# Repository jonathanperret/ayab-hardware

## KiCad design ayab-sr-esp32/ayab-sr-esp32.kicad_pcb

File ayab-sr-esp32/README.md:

# AYAB-SR-ESP32

ESP32-S3 interface board for Silver Reed knitting machines (successor of the
`ayab-silver-reed-shield` in `silverreed-firmware`). KiCad 10 project.
AYAB talks to it over Wi-Fi in normal use; USB (J2) is the fallback for users
who prefer a cable, and for flashing.

Status: schematic complete, board placed and routed (DRC: 0 unconnected, no
clearance errors). Not built yet — see *Open points* before ordering.

The schematic is a single A2 sheet split into titled sections: power input,
5 V buck, 3.3 V supply, USB (programming), user interface, solenoid buck,
current sense and limiter, mechanical, MCU, level shifting and machine
connector. Sections connect through net labels.

## Power

| Rail | Source | Notes |
|---|---|---|
| `+15V` | J1 USB-C PD, CH224A (U1) asks for 15 V, set by R1 = 56k alone (I²C not used) | Feeds both bucks |
| `Vout` / `Vsol` | U6 TPS54202; Q1 bypasses it (≈ 15 V) until an overcurrent, then it regulates at 8.05 V (R4/R24/R5 = 100k/3.3k/4.7k) | Solenoid supply, through shunt R6 (50 mΩ); `Vsol` goes to the DIN socket |
| `+5V` | U9 TPS54202, R12/R13 = 75k/10k → 5.07 V | Machine logic (DIN pin 7), U4, pull-ups R15–R18 |
| `+3.3V` | U10 AP2112K from `+5V` (D2) or J2 VBUS (D1) | ESP32, OLED, U7, U8 |

- U6 (solenoids) is enabled by the ESP32 (`SOL_EN`, 100k pull-down: off until
  the firmware turns it on). U9 is always on.
- Current limiter: U7 INA381A1 senses R6 (Kelvin connection), compares with
  a fixed threshold, and its `ALERT` output switches Q1, which pulls
  U6's FB to ground. `Vsense` (U7 VOUT, 1 V/A) is read by the ESP32.
  Threshold: R9 82k / R25 10k / R26 7.5k / R23 27k on 3.3 V gives CMPREF
  0.90 V, i.e. 0.90 A (starting values, to be confirmed on the silverreed shield;
  R24 sets the 8 V fallback, R25/R26 the threshold).
  Why 8 V: a solenoid is about 7 Ω cold (a little more once warm), so 0.9 A
  takes 6.3 V across it, plus the VCE of the carriage's Darlington driver and
  the drop in the DIN cable to the carriage.
  Hysteresis 4 µA × (12.5k + R10 82k) ≈ 0.38 V, i.e. ~0.4 A; CMPREF (0.90 V)
  stays above it, so `ALERT` always releases (RESET is tied
  to GND).

## ESP32-S3-WROOM-1 pin map

| GPIO | Module pin | Signal | Direction / notes |
|---|---|---|---|
| IO0 | 27 | `BTN_C` | S1 push (centre); also the BOOT strap: held at reset → download mode |
| IO1 | 39 | `Vsense` | ADC1_CH0, U7 output, 1 V per amp of solenoid current |
| IO2 | 38 | `Vsol_div` | ADC1_CH1, `Vsol` × 10/57 (R7 47k / R8 10k): 15 V → 2.63 V |
| IO8 | 12 | `SDA` | I²C, OLED (U5) only, 4.7k pull-ups R21/R22 |
| IO18 | 11 | `SCL` | I²C |
| IO9 | 17 | `ND1_3V` | Machine ND1 via U8 |
| IO10 | 18 | `CCP_3V` | Machine CCP (carriage clock) via U8 |
| IO11 | 19 | `HOK_3V` | Machine HOK (direction) via U8 |
| IO13 | 21 | `KSL_3V` | Machine KSL (point cam) via U8 |
| IO14 | 22 | `DOB_3V` | Output: solenoid data, to the DIN via U4 (5 V) |
| IO16 | 9 | `BTN_B` | S1 rolled toward the USB-C edge (away from the DIN) |
| IO17 | 10 | `BTN_D` | S1 rolled toward the DIN |
| IO38 | 31 | `SOL_EN` | Output: enable of the solenoid buck U6 (high = on) |
| IO39 | 32 | `PG` | CH224A power-good (open drain, 10k pull-up) |
| IO19/IO20 | 13/14 | USB D−/D+ | Native USB on J2 (through U2 ESD) |
| TXD0/RXD0 | 37/36 | J4 | UART header, not populated by default |

Firmware notes:

- Machine inputs: U8 (74LVC125, powered from 3.3 V, 5 V-tolerant inputs)
  translates the 5 V DIN signals; R15–R18 pull them up to 5 V on the DIN side,
  so `INPUT` is enough on the ESP32 side (no internal pull-up needed).
- `DOB`: U4 (74AHCT1G125 on 5 V) drives the DIN from the 3.3 V GPIO.
- Buttons: S1 common is GND → `INPUT_PULLUP`, active low.
- Avoided on purpose: IO3, IO45, IO46 (straps), IO35–IO37 (PSRAM on some
  module variants).
- The I²C bus is the OLED's only: the CH224A's CFG2/CFG3 are left open
  (single-resistor mode, R1 alone requests 15 V). Unpowered, the CH224A would
  pull them toward its dead supply (internal pull-ups) and hold the bus at
  about 2 V, below the ESP32's and the SSD1306's VIH.
- The ESP32 and the display also run with only J2 plugged in (`+3.3V` from J2
  VBUS through D1 and U10). A PD adapter plugged into J2 instead of J1 can be
  detected: `PG` stays high (the CH224A is unpowered) and no USB host enumerates
  the ESP32.

## Connectors

| Ref | Function |
|---|---|
| J1 | USB-C, power input (USB-PD 15 V) |
| J2 | USB-C, ESP32 native USB (programming, serial) |

J1 and J2 are 14.8 mm apart (centre to centre), like the USB-C ports of a
MacBook, so dual-plug MacBook cables and hubs fit both at once.
| J3 | DIN-7 female, to the knitting machine |
| J14 | 1×8 header duplicating the DIN signals (debug / alternative cable) |
| J4 | ESP32 UART0 (TX, RX), not populated |
| S1 | BL-DT 3-way thumb wheel, wheel protrudes past the top edge, under the OLED. Per the datasheet, rolling the rim 24° toward a terminal's side closes it: toward the USB-C edge → B, toward the DIN → D; push → C (common A to GND) |
| U5 | 0.91" 128×32 I²C OLED module, Hansheng HS91L02W2C01 (LCSC C5248081, SSD1306, address 0x3C), plugged into J15 on its own 2.5 mm pin spacer; any 38 × 12 mm 4-pin GND/VCC/SCL/SDA module fits. Not in the JLCPCB BOM nor the CPL: bought separately and fitted at assembly (see *Assembly-time parts*). Its far end overhangs the board edge and rests on a block of the enclosure tray |
| J15 | Low-profile 1×4 2.54 mm female socket for U5, 5.0 mm high (HC-PM254-5.0H-1x4PZ-02A, LCSC C42163122; standard sockets are 8.5 mm) |

DIN J3 and J14 pinout:

| Signal | J3 | J14 |
|---|---|---|
| ND1 | 1 | 2 |
| KSL | 2 | 3 |
| DOB | 3 | 4 |
| CCP | 4 | 5 |
| HOK | 5 | 6 |
| Vsol | 6 | 7 |
| +5V | 7 | 8 |
| GND | shield (8) | 1 |

## PCB

- 2 layers, GND pour on both sides, 64.5 × 97.1 mm (width × height), drawn in
  its intended orientation: DIN socket J3 facing up, USB-C sockets on the
  right edge. A 23.9 × 8.7 mm notch above the DIN socket leaves room for bulky
  plugs. S1's wheel sticks out of the top edge, centred on its straight part
  (x 123.9–164.5 before the antenna-side cut, see below); the OLED's visible area sits 0.5 mm further from the DIN
  than S1's axis (the HS91L02W2C01 active area is 7.62 mm from the end of
  its board, not the 7.1 mm the board was laid out for).
- Net classes: Power 0.6 mm (`+15V`, U6 switch node, `Vout`, `Vsol`),
  Supply 0.3 mm (`+5V`, `+3.3V`, LDO input, J2 VBUS), Default 0.2 mm.
- Minimum track 0.15 mm (fine-pitch escapes), minimum hole 0.2 mm (ESP32
  footprint thermal vias): within JLCPCB's standard process.
- Antenna: the ESP32 antenna is on the right edge, with a 5.6 × 47.9 mm
  cut-out under it (y 38.7–86.6, from x = 158.9: the keep-out starts at
  158.66, the 0.24 mm strip left keeps the SDA/SCL tracks 0.5 mm from the
  edge). The board was lengthened by 6 mm at the bottom so that the OLED
  module clears the keep-out: the top components (J3, U5, S1) and the top
  edge stayed in place, everything else moved down 6 mm (U5's courtyard ends
  at y 38.55, the keep-out starts at 38.7). Above the cut-out, the board is
  cut along the same line (x = 158.9) up to the top edge: the far end of the
  OLED module overhangs the board there by 5 mm and rests on a block of the
  enclosure tray. The board was then lengthened by 8 mm more at the bottom
  (nothing moved but the bottom edge and the holes).
- Mounting holes (M3, GND pad): H1 and H3 in the two bottom corners, 5.4 mm
  from the side edges and 5.3 mm from the bottom (105.4 / 116.8 and
  159.1 / 116.8), and H2 below the OLED near the right edge (155.4 / 44.5: as far
  right as the antenna keep-out allows, its lid column 2.9 mm from the OLED module).
- Routing: [UltraRoute](https://github.com/sequoia-hope/ultraroute) (commit `ddc2375`), following
  the phase-7 method of [Boardroom](https://github.com/sequoia-hope/boardroom)'s design skill,
  adapted to 2 layers and kept to 0/45/90-degree tracks. It lays the board out from bare pads, so a
  re-route is reproducible:
  - Before routing: the mechanically fixed parts locked (J1–J3, J15, U5, S1, U3, H1–H3); the GND
    pour on B.Cu only, as a soft plane (crossing it costs, `--pour-cost 3`); a GND via at every
    SMD ground pad; short links drawn from pad positions: the Kelvin pair from the inner side of
    shunt R6's pads to U7, and 0.5 mm stubs out of J1's VBUS pads; edge strips (no tracks or vias,
    pours allowed) between the USB-C, DIN and J14 pads and the board edge.
  - Rules in `ayab-sr-esp32.kicad_dru`, which both the router and KiCad's DRC apply: Power class
    at least 0.4 mm (0.6 where there is room), Supply at least 0.25 mm (0.3), except the Kelvin
    tracks inside the `kelvin-u7` area.
  - Router stages: UltraRoute's default recipe without `--tighten` (which pulls the copper taut at
    any angle) and without `--diff-pairs` (its coupled pairs are laid at any angle too; the ESP32-S3's
    USB is full-speed only, about 40 mm here, and needs no coupled routing):
    `--negotiate --rip-up --rip-boxed --prefanout --escape-room --shove-plough region --shove-reach 0.5
    --shove-repair 20 --shove-ties --guard-ties --shove-passes 60 --shove-patience 8 --strip
    --pour-cost 3 --seed N --threads 1 --timeout 240`, nice'd, one run at a time.
  - Seeds 0–9 tried, each judged by KiCad after restoring the F.Cu pour and refilling (all clean);
    seed 9 kept for its short 15 V buck switch node (11.1 mm, no via) and bootstrap (1.9 mm, no
    via: C4 sits beside U6, its pads 2.7 mm from BOOT and 3.6 mm from SW).
  - After routing: GND pours on both sides, stitching vias on a 3 mm grid, dangling copper
    removed, all copper unlocked (only the parts above stay locked); then `octofix.py` turns every
    segment off a multiple of 45 degrees into a 45-degree leg and an orthogonal leg (ends unmoved,
    the variant KiCad's DRC accepts), and collinear pieces are merged. 99.7% of the track length is
    at 0/45/90 degrees; what is left is 32 pad entries of at most 0.3 mm and 2 short jogs.
  - Checks: DRC 0 errors and 0 unconnected with every severity on (`min_connection` 0.127 mm;
    dangling tracks and vias, slivers, isolated copper and connection width as errors); every pad's
    best joint at least min(0.15 mm, track width); B.Cu ground in one piece (5138 mm²), stitched to
    the F.Cu pour.
  - Against the Freerouting route: 2093 mm of track instead of 2059 mm, 79 signal and power
    vias plus 452 GND vias (45 at ground pads, the rest stitching), B.Cu ground in 1 piece instead of 14, and power tracks at
    their class widths (the old route had 90 power tracks under them).
  - The driver and the board's routing inputs are on the `tooling` branch
    (`scripts/kicad/route/ultraroute/`, `ayab-sr-esp32/tools/ultraroute/`): `route.sh ayab-sr-esp32 WORK 9`,
    then `finish.sh WORK/j9 WORK/final`, regenerates this board.
  - Placement finding: J1's VBUS pads sit between the CC pins, so its stubs are 0.5 mm, not 0.6.

3D models: `ayab-library/packages3D/OLED_0.91_128x32_I2C.step` (generated by
`packages3D/generators/oled_0.91_128x32_step.py`, raised 5 mm by the U5 footprint for the socket),
`PinSocket_1x04_P2.54mm_Vertical_H5.0.step` for J15 (`packages3D/generators/pin_socket_1x04_h5_step.py`) and `SW-SMD_BL-DT.step` for S1 (CadQuery,
`packages3D/generators/sw_smd_bl_dt_step.py`, from the manufacturer's drawing).

A 3D-printable enclosure is in [`enclosure/`](enclosure/README.md).
Its model follows the board's 90° turn (`board_frame()` in the .scad), the
current outline and holes, the OLED on its 5 mm socket (lid raised by 5 mm) and the block under
the OLED's far end. A redesign is planned (ring around the machine's mast).

## Renders

Board renders come from KiCad (`kicad-cli pcb render`), enclosure renders from
OpenSCAD's preview (`enclosure/tools/quick_render.py`) and the 2D sections
from `enclosure/tools/sections.py`. MP4 versions of the enclosure animations:
[turntable](enclosure/renders/turntable.mp4),
[exploded](enclosure/renders/exploded.mp4).

### Interactive 3D view

[`viewer/`](viewer/) is a three.js page: the board (KiCad GLB export with
silkscreen and soldermask) in its tray and lid, with orbit and zoom, an explode
slider, preset views, toggles for the silkscreen and the copper traces
(`traces.json`, drawn at their true width but raised 0.1 mm and coloured: copper
on top, blue underneath), and a click on a part shows its reference, value and
LCSC number. It needs to be served
over HTTP, e.g. GitHub Pages, or locally:

    python3 -m http.server -d ayab-sr-esp32/viewer 8000   # then open http://localhost:8000

### Board

<table>
<tr><td align="center"><br><sub>Front isometric</sub></td><td align="center"><br><sub>Back isometric</sub></td></tr>
<tr><td align="center"><br><sub>Top</sub></td><td align="center"><br><sub>Bottom</sub></td></tr>
</table>

### Enclosure

<table>
<tr><td align="center"><br><sub>Assembled</sub></td><td align="center"><br><sub>Assembled, DIN and wheel side</sub></td></tr>
<tr><td align="center"><br><sub>X-ray (transparent lid)</sub></td><td align="center"><br><sub>Exploded</sub></td></tr>
<tr><td align="center"><br><sub>Tray with the board</sub></td><td align="center"><br><sub>Tray</sub></td></tr>
<tr><td align="center"><br><sub>Lid, top</sub></td><td align="center"><br><sub>Lid, underside</sub></td></tr>
<tr><td align="center"><br><sub>USB-C side</sub></td><td align="center"><br><sub>DIN and wheel side</sub></td></tr>
<tr><td align="center"><br><sub>Turntable</sub></td><td align="center"><br><sub>Exploded, animated</sub></td></tr>
</table>

### Enclosure sections

<table>
<tr><td align="center"><br><sub>Through the wheel S1 and the OLED</sub></td><td align="center"><br><sub>Through the DIN socket axis</sub></td></tr>
<tr><td align="center"><br><sub>Through the USB-C J1</sub></td><td align="center"><br><sub>Through the H2 column</sub></td></tr>
<tr><td align="center"><br><sub>Through the OLED support block</sub></td><td></td></tr>
</table>

## Production files

`production/` holds outputs generated with `kicad-cli` 10.0.7 from this
revision: Gerbers and Excellon drill files (`gerbers/`, zipped in
`ayab-sr-esp32-gerbers.zip`), the BOM (`ayab-sr-esp32-bom.csv`, grouped, with
an LCSC number on every placed part), the pick-and-place file
(`ayab-sr-esp32-pos.csv`, plus `ayab-sr-esp32-cpl-jlc.csv` in JLCPCB's CPL format with
the `FT Rotation Offset` corrections applied) and the schematic PDF. Regenerate them after
any change (scripts on the `tooling` branch).

### Ordering the parts from LCSC (self-assembly)

The BOM's LCSC numbers are chosen for JLCPCB assembly (basic parts where possible). For a direct
LCSC order, one substitute applies while LCSC's own stock of the BOM part is empty:

- **C3, C12, C14, C15** (100 nF 0603, BOM C14663, a JLCPCB basic part with plenty of JLCPCB
  stock): order **C1591** (Samsung CL10B104KB8NNNC, 100 nF X7R 50 V 0603) from LCSC instead.
  Keep C14663 in the BOM: C1591 is an extended part at JLCPCB (about $3 more per assembly order).

Parts for 5 boards cost about $56 at LCSC (November 2026 prices, minimum order quantities
applied, OLED module, shipping and import duties not included).

## Assembly-time parts

JLCPCB assembles everything in the BOM and CPL, J15 included. One part is not in either and is
fitted by the assembler:

- **OLED module U5**: 0.91" 128×32 I²C module (Hansheng HS91L02W2C01, LCSC C5248081, or any
  38 × 12 mm SSD1306 module), 3.3 V supply, 4 pins at 2.54 mm in the order **GND, VCC, SCL, SDA**
  (pin 1 = GND: the square pad of J15, the one farthest from the top edge). It needs a 4-pin male header
  soldered on: check whether your module comes with the header soldered (the LCSC part appears to
  ship without one, going by its datasheet drawing).
- **Fitting**: plug it into J15 (5.0 mm low-profile socket), glass up, the module overhanging the
  board edge on the antenna side. The header's 2.5 mm plastic spacer rests on top of J15; the pins
  below it go into the socket, whose contacts are about 4.5 mm deep. Standard headers have about
  6 mm below the spacer: if the module does not sit flat on the socket, trim the pins to about
  4 mm below the spacer. The enclosure has no trimming jig.
- **Support**: the far end of the module rests on a block of the enclosure tray (0.1 mm below the
  module), in the space next to the board edge.

## Tooling

The scripts used to edit, check, route and regenerate this board (and the matching workflow skill)
live on the `tooling` branch.

## Open points

- CH224A (checked in the WCH CH224 manual v2.1): PG is open drain, active low,
  rated 32 V, so R20 is right; CFG2/CFG3 may float in single-resistor mode
  (§5.2.1), so they are left unconnected.
- Wi-Fi is the main link, so the antenna matters most. The OLED module is
  now clear of the antenna keep-out. On the first boards, measure RSSI and
  throughput with the board in its enclosure and mounted on the machine (a
  large metal body: the antenna end should face away from it). If range is
  short: use the ESP32-S3-WROOM-1U (u.FL) with a small external antenna
  (about $0.5–1 more).
- Also on the first boards: scope the 3.3 V rail during Wi-Fi transmit bursts
  (350–500 mA peaks on the AP2112K) with the solenoids firing, the bucks'
  switching noise, and the Vsense / Vsol_div ADC readings. These measurements
  decide whether the first respin goes to 4 layers (solid GND plane under
  the module and the bucks).
- DRC: clean. `ayab-sr-esp32.kicad_dru` has
  the JLCPCB 2-layer rules plus two documented exceptions: U5 stands on its
  socket above J15 and S1 (courtyard overlap), and the silkscreen of parts
  that overhang the board edge (U3, U5, J3) is clipped by the fab.

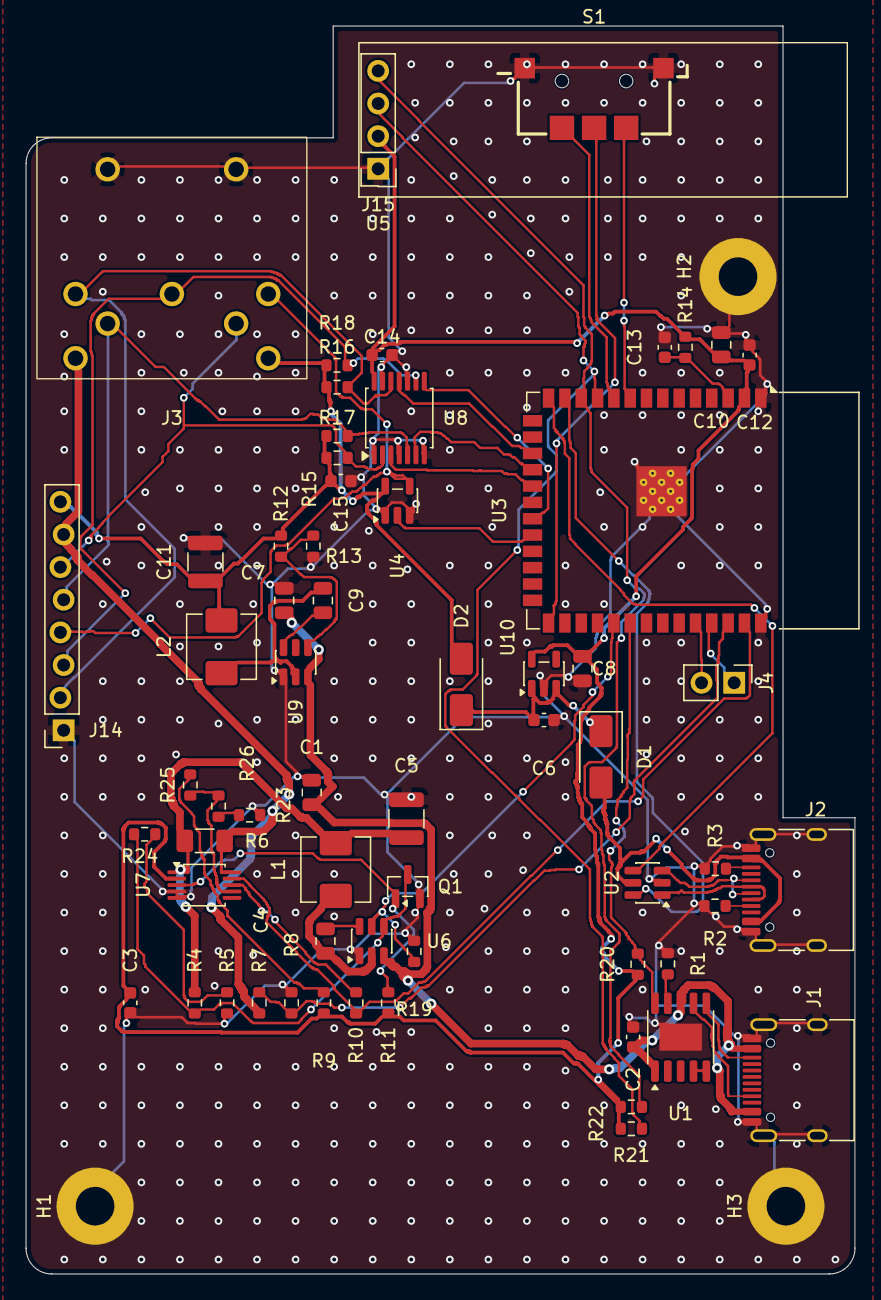
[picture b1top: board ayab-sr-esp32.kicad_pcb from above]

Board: 2 copper layers, 64.5 x 97.1 mm, 66 parts (0 on the bottom side), 52 nets.

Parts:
C1, C7, C8: 10u; C_0805_2012Metric
C2, C6, C13: 1u; C_0603_1608Metric
C3, C12, C14, C15: 100n; C_0603_1608Metric
C4, C9: 100n; C_0805_2012Metric
C5, C11: 47u; C_1210_3225Metric
C10: 22u; C_0805_2012Metric
D1, D2: SS34; D_SMA
H1, H2, H3: MountingHole_Pad; MountingHole_3mm_Pad
J1, J2: USB_C_Receptacle_USB2.0_16P; USB_C_Receptacle_HRO_TYPE-C-31-M-12
J3: DIN-7; DIN-704-M10
J4: Conn_01x02; PinHeader_1x02_P2.54mm_Vertical
J14: Conn_01x08; PinSocket_1x08_P2.54mm_Vertical_Lock
J15: HC-PM254-5.0H-1x4PZ-02A; PinSocket_1x04_P2.54mm_Vertical_H5.0
L1, L2: 10u; L_Changjiang_FXL0518
Q1: BSS138; SOT-23
R1: 56k; R_0603_1608Metric
R2, R3: 5.1k; R_0603_1608Metric
R4, R19: 100k; R_0603_1608Metric
R5, R21, R22: 4.7k; R_0603_1608Metric
R6: 50m; R_1206_3216Metric_Pad1.30x1.75mm_HandSolder
R7: 47k; R_0603_1608Metric
R8, R11, R13, R14, R15, R16, R17, R18, R20, R25: 10k; R_0603_1608Metric
R9, R10: 82k; R_0603_1608Metric
R12: 75k; R_0603_1608Metric
R23: 27k; R_0603_1608Metric
R24: 3.3k; R_0603_1608Metric
R26: 7.5k; R_0603_1608Metric
S1: BL-DT; SW-SMD_BL-DT
U1: CH224A; SSOP-10-1EP_3.9x4.9mm_P1mm_EP2.1x3.3mm
U2: USBLC6-2SC6; SOT-23-6
U3: ESP32-S3-WROOM-1
U4: 74AHCT1G125; SOT-23-5
U5: HS91L02W2C01; OLED_0.91_128x32_I2C_Module_Socket_H5.0
U6, U9: TPS54202; SOT-23-6
U7: INA381A1; TSSOP-10_3x3mm_P0.5mm
U8: 74LVC125; TSSOP-14_4.4x5mm_P0.65mm
U10: AP2112K-3.3; SOT-23-5

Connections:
+3.3V: C3.2, C8.1, C10.1, C12.1, C14.1, J15.2, R9.1, R11.1, R14.1, R20.1, R21.1, R22.1, U3.2 (3V3), U7.2 (VS), U8.14 (VCC), U10.5 (VOUT)
+5V: C11.1, C15.2, D2.2 (A), J3.7, J14.8, L2.2, R12.2, R15.1, R16.1, R17.1, R18.1, U4.5 (VCC)
+15V: C1.1, C2.1, C7.1, J1.A4 (VBUS), J1.A9 (VBUS), J1.B4 (VBUS), J1.B9 (VBUS), U1.1 (VHV), U1.8 (VBUS), U6.3 (VIN), U9.3 (VIN)
/ALERT: Q1.1 (G), R11.2, U7.3 (~ALERT)
/BTN_B: S1.B, U3.9 (IO16)
/BTN_C: S1.C, U3.27 (IO0)
/BTN_D: S1.D, U3.10 (IO17)
/CCP: J3.4, J14.5, R17.2, U8.5 (2A)
/CCP_3V: U3.18 (IO10), U8.6 (2Y)
/CFG1: R1.1, U1.9 (CFG1)
/CMPREF: R25.2, R26.1, U7.7 (CMPREF)
/DOB: J3.3, J14.4, U4.4
/DOB_3V: U3.22 (IO14), U4.2
/FB: Q1.3 (D), R4.1, R24.1, U6.4 (FB)
/HOK: J3.5, J14.6, R15.2, U8.2 (1A)
/HOK_3V: U3.19 (IO11), U8.3 (1Y)
/KSL: J3.2, J14.3, R16.2, U8.9 (3A)
/KSL_3V: U3.21 (IO13), U8.8 (3Y)
/ND1: J3.1, J14.2, R18.2, U8.12 (4A)
/ND1_3V: U3.17 (IO9), U8.11 (4Y)
/PG: R20.2, U1.10 (PG), U3.32 (IO39)
/SCL: J15.3, R22.2, U3.11 (IO18)
/SDA: J15.4, R21.2, U3.12 (IO8)
/SOL_EN: R19.1, U3.31 (IO38), U6.5 (EN)
/USB2_VBUS: D1.2 (A), J2.A4 (VBUS), J2.A9 (VBUS), J2.B4 (VBUS), J2.B9 (VBUS), U2.5 (VBUS)
/USB_DM: U2.6 (I/O1), U3.13 (USB_D-)
/USB_DP: U2.4 (I/O2), U3.14 (USB_D+)
/Vout: C5.1, L1.2, R4.2, R6.1, U7.1 (IN+)
/Vsense: R10.1, U3.39 (IO1), U7.9 (VOUT)
/Vsol: J3.6, J14.7, R6.2, R7.1, U7.10 (IN-)
/Vsol_div: R7.2, R8.1, U3.38 (IO2)
GND: C1.2, C2.2, C3.1, C5.2, C6.2, C7.2, C8.2, C10.2, C11.2, C12.2, C13.2, C14.2, C15.1, H1.1 (1_1), H2.1 (1_1), H3.1 (1_1), J1.A1 (GND), J1.A12 (GND), J1.B1 (GND), J1.B12 (GND), J1.SH (SHIELD), J2.A1 (GND), J2.A12 (GND), J2.B1 (GND), J2.B12 (GND), J2.SH (SHIELD), J3.8 (GND_8), J14.1, J15.1, Q1.2 (S), R1.2, R2.2, R3.2, R5.1, R8.2, R13.1, R19.2, R23.2, S1.A, U1.11 (GND), U2.2 (GND), U3.1 (GND), U3.40 (GND), U3.41 (GND), U4.1, U4.3 (GND), U6.1 (GND), U7.4 (RESET), U7.5 (GND), U8.1 (~1OE), U8.4 (~2OE), U8.7 (GND), U8.10 (~3OE), U8.13 (~4OE), U9.1 (GND), U10.2 (GND)
unnamed: C6.1, D1.1 (K), D2.1 (K), U10.1 (VIN), U10.3 (EN)
unnamed: J1.A5 (CC1), U1.7 (CC1)
unnamed: J1.B5 (CC2), U1.6 (CC2)
unnamed: J2.A5 (CC1), R2.1
unnamed: J2.B5 (CC2), R3.1
unnamed: J2.A6 (D+), J2.B6 (D+), U2.3 (I/O2)
unnamed: J2.A7 (D-), J2.B7 (D-), U2.1 (I/O1)
unnamed: J4.1, U3.37 (TXD0)
unnamed: J4.2, U3.36 (RXD0)
unnamed: R23.1, R26.2
unnamed: R5.2, R24.2
unnamed: R9.2, R25.1
unnamed: U1.4 (DP), U1.5 (DM)
unnamed: C13.1, R14.2, U3.3 (EN)
unnamed: C4.1, U6.6 (BOOT)
unnamed: C4.2, L1.1, U6.2 (SW)
unnamed: R10.2, U7.8 (CMPIN)
unnamed: C9.1, U9.6 (BOOT)
unnamed: R12.1, R13.2, U9.4 (FB)
unnamed: C9.2, L2.1, U9.2 (SW)

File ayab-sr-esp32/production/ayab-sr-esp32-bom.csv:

"Designator","Value","Footprint","LCSC","Qty","DNP"
"C1,C7,C8","10u","Capacitor_SMD:C_0805_2012Metric","C15850","3",""
"C2,C6,C13","1u","Capacitor_SMD:C_0603_1608Metric","C15849","3",""
"C3,C12,C14,C15","100n","Capacitor_SMD:C_0603_1608Metric","C14663","4",""
"C4,C9","100n","Capacitor_SMD:C_0805_2012Metric","C49678","2",""
"C5,C11","47u","Capacitor_SMD:C_1210_3225Metric","C7432791","2",""
"C10","22u","Capacitor_SMD:C_0805_2012Metric","C45783","1",""
"D1,D2","SS34","Diode_SMD:D_SMA","C8678","2",""
"J1,J2","USB_C_Receptacle_USB2.0_16P","Connector_USB:USB_C_Receptacle_HRO_TYPE-C-31-M-12","C165948","2",""
"J3","DIN-7","Library:DIN-704-M10","C20611695","1",""
"J15","HC-PM254-5.0H-1x4PZ-02A","Library:PinSocket_1x04_P2.54mm_Vertical_H5.0","C42163122","1",""
"L1,L2","10u","Inductor_SMD:L_Changjiang_FXL0518","C475910","2",""
"Q1","BSS138","Package_TO_SOT_SMD:SOT-23","C7420339","1",""
"R1","56k","Resistor_SMD:R_0603_1608Metric","C23206","1",""
"R2,R3","5.1k","Resistor_SMD:R_0603_1608Metric","C23186","2",""
"R4,R19","100k","Resistor_SMD:R_0603_1608Metric","C25803","2",""
"R5,R21,R22","4.7k","Resistor_SMD:R_0603_1608Metric","C23162","3",""
"R6","50m","Resistor_SMD:R_1206_3216Metric_Pad1.30x1.75mm_HandSolder","C127691","1",""
"R7","47k","Resistor_SMD:R_0603_1608Metric","C25819","1",""
"R8,R11,R13,R14,R15,R16,R17,R18,R20,R25","10k","Resistor_SMD:R_0603_1608Metric","C25804","10",""
"R9,R10","82k","Resistor_SMD:R_0603_1608Metric","C23254","2",""
"R12","75k","Resistor_SMD:R_0603_1608Metric","C23242","1",""
"R23","27k","Resistor_SMD:R_0603_1608Metric","C22967","1",""
"R24","3.3k","Resistor_SMD:R_0603_1608Metric","C22978","1",""
"R26","7.5k","Resistor_SMD:R_0603_1608Metric","C23234","1",""
"S1","BL-DT","Library:SW-SMD_BL-DT","C53223909","1",""
"U1","CH224A","Package_SO:SSOP-10-1EP_3.9x4.9mm_P1mm_EP2.1x3.3mm","C42459160","1",""
"U2","USBLC6-2SC6","Package_TO_SOT_SMD:SOT-23-6","C2687116","1",""
"U3","ESP32-S3-WROOM-1","RF_Module:ESP32-S3-WROOM-1","C2913198","1",""
"U4","74AHCT1G125","Package_TO_SOT_SMD:SOT-23-5","C52140417","1",""
"U6,U9","TPS54202","Package_TO_SOT_SMD:SOT-23-6","C191884","2",""
"U7","INA381A1","Package_SO:TSSOP-10_3x3mm_P0.5mm","C1849472","1",""
"U8","74LVC125","Package_SO:TSSOP-14_4.4x5mm_P0.65mm","C54411083","1",""
"U10","AP2112K-3.3","Package_TO_SOT_SMD:SOT-23-5","C22365427","1",""

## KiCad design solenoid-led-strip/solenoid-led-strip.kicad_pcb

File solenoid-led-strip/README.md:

# Solenoid LED strip for Brother electronic knitting machines

This board is meant to be used as a debugging aid when working on alternative electronics for the Brother KH-9xx series, such as [AYAB](https://github.com/AllYarnsAreBeautiful). But as it simply inserts itself between the electronics and the solenoids, it can also be used with the machine's original electronics, to understand how they drive the solenoids.

I have not built the board described by this KiCad project yet, only a prototype from the schematic. No guarantee of any kind is offered as to the suitability of these files for producing a working device.

## Prototype board

This board I built uses the same schematic:

## Mockup

## Schematic

## Tracks

## [Interactive view](https://kicanvas.org/?github=https%3A%2F%2Fgithub.com%2Fjonathanperret%2Fayab-hardware%2Ftree%2Fsolenoid-led-strip%2Fsolenoid-led-strip) courtesy of [KiCanvas](https://kicanvas.org)

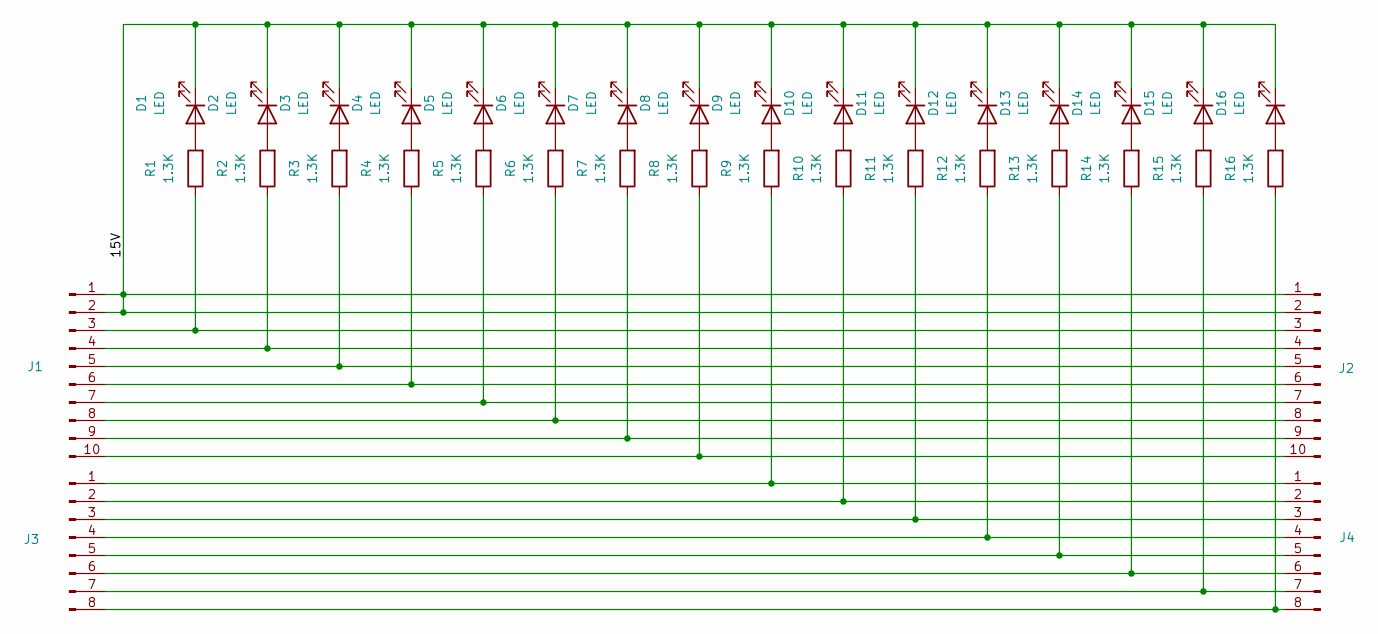
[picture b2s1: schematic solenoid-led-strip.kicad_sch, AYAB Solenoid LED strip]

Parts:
D1, D2, D3, D4, D5, D6, D7, D8, D9, D10, D11, D12, D13, D14, D15, D16: LED; LED_0805_2012Metric
J1: PinHeader_1x10_P2.54mm_Vertical
J2: PinHeader_1x10_P2.54mm_Horizontal
J3: PinHeader_1x08_P2.54mm_Vertical
J4: PinHeader_1x08_P2.54mm_Horizontal
R1, R2, R3, R4, R5, R6, R7, R8, R9, R10, R11, R12, R13, R14, R15, R16: 1.3K; R_0805_2012Metric

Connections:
/15V: D1.1 (K), D2.1 (K), D3.1 (K), D4.1 (K), D5.1 (K), D6.1 (K), D7.1 (K), D8.1 (K), D9.1 (K), D10.1 (K), D11.1 (K), D12.1 (K), D13.1 (K), D14.1 (K), D15.1 (K), D16.1 (K), J1.1, J1.2, J2.1, J2.2
unnamed: D1.2 (A), R1.2
unnamed: D2.2 (A), R2.2
unnamed: D3.2 (A), R3.2
unnamed: D4.2 (A), R4.2
unnamed: D5.2 (A), R5.2
unnamed: D6.2 (A), R6.2
unnamed: D7.2 (A), R7.2
unnamed: D8.2 (A), R8.2
unnamed: D9.2 (A), R9.2
unnamed: D10.2 (A), R10.2
unnamed: D11.2 (A), R11.2
unnamed: D12.2 (A), R12.2
unnamed: D13.2 (A), R13.2
unnamed: D14.2 (A), R14.2
unnamed: D15.2 (A), R15.2
unnamed: D16.2 (A), R16.2
unnamed: J1.3, J2.3, R1.1
unnamed: J1.4, J2.4, R2.1
unnamed: J1.5, J2.5, R3.1
unnamed: J1.6, J2.6, R4.1
unnamed: J1.7, J2.7, R5.1
unnamed: J1.8, J2.8, R6.1
unnamed: J1.9, J2.9, R7.1
unnamed: J1.10, J2.10, R8.1
unnamed: J3.1, J4.1, R9.1
unnamed: J3.2, J4.2, R10.1
unnamed: J3.3, J4.3, R11.1
unnamed: J3.4, J4.4, R12.1
unnamed: J3.5, J4.5, R13.1
unnamed: J3.6, J4.6, R14.1
unnamed: J3.7, J4.7, R15.1
unnamed: J3.8, J4.8, R16.1

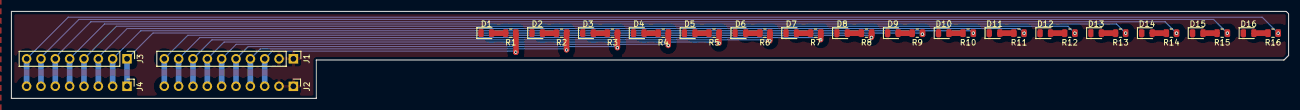
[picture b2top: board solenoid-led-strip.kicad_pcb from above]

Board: 2 copper layers, 226.2 x 15.4 mm, 36 parts (0 on the bottom side), 33 nets.

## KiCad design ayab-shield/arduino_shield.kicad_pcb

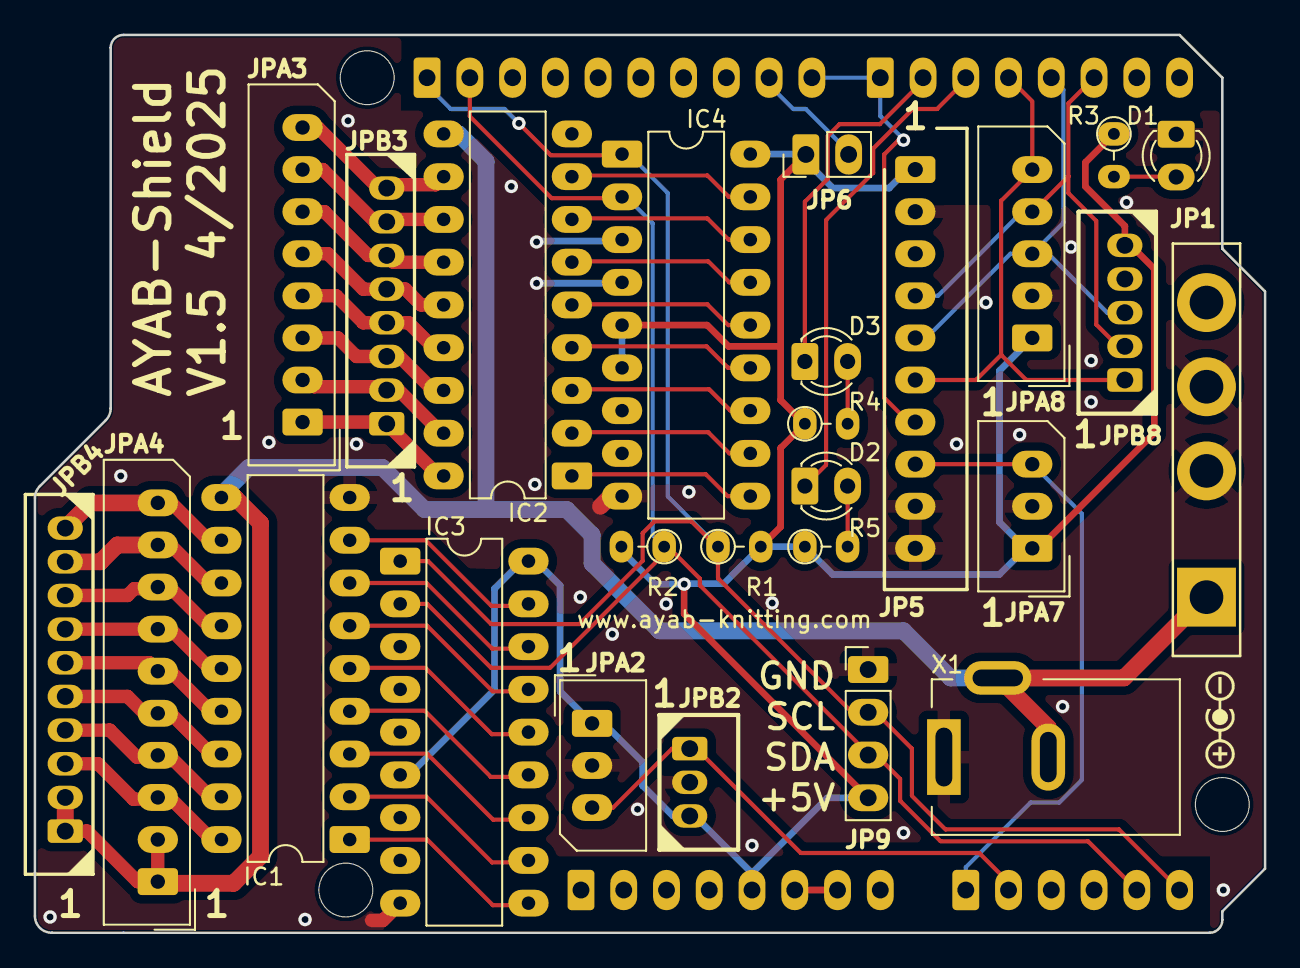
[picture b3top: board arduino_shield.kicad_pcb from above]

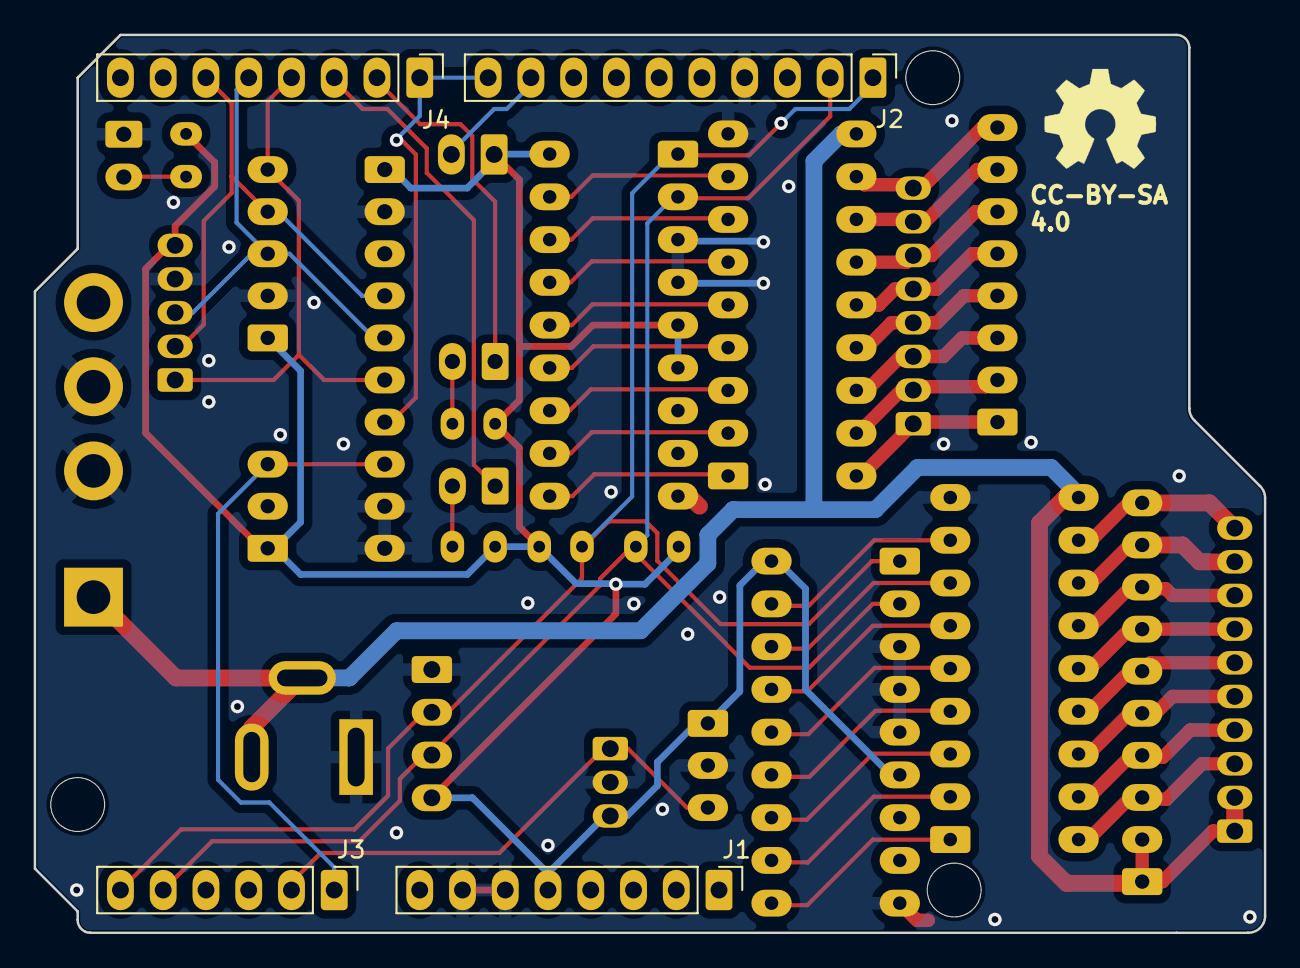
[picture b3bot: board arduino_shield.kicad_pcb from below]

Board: 2 copper layers, 73.1 x 53.3 mm, 33 parts (4 on the bottom side), 49 nets.

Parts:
D1: RED_3MM; LED_D3.0mm
D2: YEL_3MM; LED_D3.0mm
D3: GRN_3MM; LED_D3.0mm
IC1, IC2: ULN2803A; DIP-18_W7.62mm_LongPads
IC3, IC4: MCP2300X/P; DIP-18_W7.62mm_LongPads
J1: Power; PinHeader_1x08_P2.54mm_Vertical
J2: Digital/PWM; PinHeader_1x10_P2.54mm_Vertical
J3: Analog; PinHeader_1x06_P2.54mm_Vertical
J4: Digital/PWM; PinHeader_1x08_P2.54mm_Vertical
JP1: BROTHER POWER; Brother_4P
JP5: 1X10 2.5mm; SHDR10W70P0X250_1X10_2740X490X590P
JP6: 1x2 2.5mm; PinHeader_1x02_P2.54mm_Vertical
JP9: 1X5 2.5mm; PinHeader_1x04_P2.54mm_Vertical
JPA2, JPA7: 1X3 2.5mm; Molex_SPOX_5267-03A_1x03_P2.50mm_Vertical
JPA3: 1X8 2.5mm; Molex_SPOX_5267-08A_1x08_P2.50mm_Vertical
JPA4: 1X10 2.5mm; Molex_SPOX_5267-10A_1x10_P2.50mm_Vertical
JPA8: 1X5 2.5mm; Molex_SPOX_5267-05A_1x05_P2.50mm_Vertical
JPB2: 1X3 2mm; CONN-TH_3P-P2.00_A2004WV-3P
JPB3: 1X8 2mm; 530140810
JPB4: 1X10 2mm; 530141010
JPB8: 1X5 2mm; CONN-TH_A2004WV-5P
MH1, MH2, MH4: MountingHole_3.2mm
R1, R2: 4K7; R_Axial_DIN0204_L3.6mm_D1.6mm_P2.54mm_Vertical
R3, R4, R5: 150; R_Axial_DIN0204_L3.6mm_D1.6mm_P2.54mm_Vertical
X1: KLDX-0202-AC; BarrelJack_Kycon_KLDX-0202-xC_Horizontal

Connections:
+5V: IC3.6 (~RESET), IC3.18 (VDD), IC4.5 (A0), IC4.6 (~RESET), IC4.18 (VDD), J1.5, JP5.1, JP6.1, JP9.4, JPA2.1, JPA7.1, JPA8.1, JPB2.3, JPB8.5, R1.2, R2.2, R3.1, R4.1, R5.1
+15V: IC1.10 (COM), IC2.10 (COM), JP1.1 (+15V), JPA4.1, JPA4.2, JPB4.1, JPB4.2, X1.2, X1.3
/910_L: J2.10, J4.1, JP5.7
/BUZZ: J2.9, JP6.2
/ENC_A: J4.6, JP5.4, JPA8.4, JPB8.2
/ENC_B: J4.5, JP5.5, JPA8.3, JPB8.3
/ENC_C: J4.4, JP5.6, JPA8.5, JPB8.1
/EOL_L: J3.2, JPA2.3, JPB2.1
/EOL_R: J3.1, JP5.8, JPA7.3
/LED_GRN: D3.1 (K), J4.2
/LED_YEL: D2.1 (K), J4.3
/SCL: IC3.1 (SCL), IC4.1 (SCL), J2.1, J3.6, JP9.2, R1.1
/SDA: IC3.2 (SDA), IC4.2 (SDA), J2.2, J3.5, JP9.3, R2.1
GND: D1.1 (K), IC1.9 (GND), IC2.9 (GND), IC3.3 (A2), IC3.4 (A1), IC3.5 (A0), IC3.9 (VSS), IC4.3 (A2), IC4.4 (A1), IC4.9 (VSS), J1.6, J1.7, J2.4, JP1.2 (GND), JP1.3 (GND), JP5.2, JP5.9, JP5.10, JP9.1, JPA2.2, JPA7.2, JPA8.2, JPB2.2, JPB8.4, X1.1
unnamed: D1.2 (A), R3.2
unnamed: D2.2 (A), R5.2
unnamed: D3.2 (A), R4.2
unnamed: IC1.1 (I1), IC3.10 (GP0)
unnamed: IC1.2 (I2), IC3.11 (GP1)
unnamed: IC1.3 (I3), IC3.12 (GP2)
unnamed: IC1.4 (I4), IC3.13 (GP3)
unnamed: IC1.5 (I5), IC3.14 (GP4)
unnamed: IC1.6 (I6), IC3.15 (GP5)
unnamed: IC1.7 (I7), IC3.16 (GP6)
unnamed: IC1.8 (I8), IC3.17 (GP7)
unnamed: IC1.18 (O1), JPA4.3, JPB4.3
unnamed: IC1.17 (O2), JPA4.4, JPB4.4
unnamed: IC1.16 (O3), JPA4.5, JPB4.5
unnamed: IC1.15 (O4), JPA4.6, JPB4.6
unnamed: IC1.14 (O5), JPA4.7, JPB4.7
unnamed: IC1.13 (O6), JPA4.8, JPB4.8
unnamed: IC1.12 (O7), JPA4.9, JPB4.9
unnamed: IC1.11 (O8), JPA4.10, JPB4.10
unnamed: IC2.1 (I1), IC4.10 (GP0)
unnamed: IC2.2 (I2), IC4.11 (GP1)
unnamed: IC2.3 (I3), IC4.12 (GP2)
unnamed: IC2.4 (I4), IC4.13 (GP3)
unnamed: IC2.5 (I5), IC4.14 (GP4)
unnamed: IC2.6 (I6), IC4.15 (GP5)
unnamed: IC2.7 (I7), IC4.16 (GP6)
unnamed: IC2.8 (I8), IC4.17 (GP7)
unnamed: IC2.18 (O1), JPA3.1, JPB3.1
unnamed: IC2.17 (O2), JPA3.2, JPB3.2
unnamed: IC2.16 (O3), JPA3.3, JPB3.3
unnamed: IC2.15 (O4), JPA3.4, JPB3.4
unnamed: IC2.14 (O5), JPA3.5, JPB3.5
unnamed: IC2.13 (O6), JPA3.6, JPB3.6
unnamed: IC2.12 (O7), JPA3.7, JPB3.7
unnamed: IC2.11 (O8), JPA3.8, JPB3.8

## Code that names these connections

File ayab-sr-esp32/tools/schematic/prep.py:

"""Net naming and text fixes, applied to base.kicad_sch (the hand-drawn schematic) before layout.py (old coordinates)."""
import re, sys, uuid
from sx import *
t = open(sys.argv[1]).read()
_n = [0]
def U():
    _n[0] += 1
    return str(uuid.uuid5(uuid.NAMESPACE_URL, "ayab-sr-esp32-prep-%d" % _n[0]))

def label(name, x, y, ang):
    j = 'left bottom' if ang == 0 else 'right bottom'
    return ('\t(label "%s"\n\t\t(at %g %g %d)\n\t\t(effects\n\t\t\t(font\n\t\t\t\t(size 1.27 1.27)\n\t\t\t)\n'
            '\t\t\t(justify %s)\n\t\t)\n\t\t(uuid "%s")\n\t)\n') % (name, x, y, ang, j, U())

def is_wire(s, p, q):
    P = [tuple(map(float, m)) for m in re.findall(r'\(xy ([-\d.]+) ([-\d.]+)\)', s)]
    return head(s) == 'wire' and set(P) == {p, q}

LCSC = {'C2': 'C15849', 'R1': 'C23206', 'R2': 'C23186', 'R3': 'C23186', 'R7': 'C25819', 'R13': 'C25804',
        'D1': 'C8678', 'D2': 'C8678', 'J1': 'C165948', 'J2': 'C165948', 'J3': 'C20611695', 'U1': 'C42459160',
        'U2': 'C2687116', 'U3': 'C2913198', 'U4': 'C52140417', 'U5': 'C5248081', 'U8': 'C54411083', 'U10': 'C22365427'}

def set_lcsc(s, code):
    if '(property "LCSC" ' in s:
        return re.sub(r'\(property "LCSC" "[^"]*"', '(property "LCSC" "%s"' % code, s, count=1)
    at = re.search(r'\n\t\t\(at ([-\d.]+) ([-\d.]+)', s)
    blk = ('\t\t(property "LCSC" "%s"\n\t\t\t(at %s %s 0)\n\t\t\t(hide yes)\n\t\t\t(show_name no)\n\t\t\t(do_not_autoplace no)\n'
           '\t\t\t(effects\n\t\t\t\t(font\n\t\t\t\t\t(size 1.27 1.27)\n\t\t\t\t)\n\t\t\t)\n\t\t)\n') % (code, at.group(1), at.group(2))
    i = s.index('\t\t(pin "')
    return s[:i] + blk + s[i:]

def set_field(s, name, x, y, ang, just):
    def f(m):
        body = m.group(0)
        body = re.sub(r'\(at [^)]*\)', '(at %g %g %d)' % (x, y, ang), body, count=1)
        body = re.sub(r'\n\t\t\t\t\(justify [^)]*\)', '', body)
        if just: body = body.replace('\n\t\t\t\t)\n\t\t\t)', '\n\t\t\t\t)\n\t\t\t\t(justify %s)\n\t\t\t)' % just, 1)
        return body
    return re.sub(r'\(property "%s" "[^"]*"\n.*?\n\t\t\)' % name, f, s, count=1, flags=re.S)

pwr = sorted(int(n) for n in re.findall(r'"#PWR0*(\d+)"', t))
next_pwr = pwr[-1] + 1
out = []; last = 0
for a, b in items(t):
    s = t[a:b]; h = head(s); out.append(t[last:a]); last = b
    # ALERT: cut the R11 junction -> Q1 gate link, name both sides
    if is_wire(s, (419.1, 137.16), (419.1, 134.62)): out.append('\x00'); continue
    if h == 'junction' and '(at 419.1 134.62)' in s: out.append('\x00'); continue
    # Buck5V -> +5V
    if h == 'label' and s.startswith('(label "Buck5V"'):
        if '(at 303.53 200.66' in s: out.append('\x00'); continue
        # replace D2's Buck5V label with a +5V power symbol pointing left
        tpl = re.search(r'\(symbol\n\t\t\(lib_id "power:\+5V"\).*?\n\t\)', t, re.S).group(0)
        ref = '#PWR%03d' % next_pwr
        p = re.sub(r'"#PWR\d+"', '"%s"' % ref, tpl)
        p = re.sub(r'\(uuid "[^"]+"\)', lambda m: '(uuid "%s")' % U(), p)
        p = re.sub(r'\n\t\t\(fields_autoplaced yes\)', '', p)
        p = re.sub(r'\(at [-\d.]+ [-\d.]+ \d+\)', '(at 123.19 81.28 0)', p)
        p = set_field(p, 'Value', 123.19, 77.47, 0, None)
        out.append(p); continue
    if h == 'symbol':
        r = re.search(r'\(property "Reference" "([^"]+)"', s).group(1)
        if r in LCSC:
            s = set_lcsc(s, LCSC[r])
        if r in ('H1', 'H2', 'H3'):
            s = s.replace('\n\t\t(in_bom yes)', '\n\t\t(in_bom no)', 1)   # mounting holes: no BOM line for JLCPCB
        if r == 'U5':
            # Hansheng HS91L02W2C01: same 38 x 12 mm 4-pin module outline as the ER-OLEDM0.91, stocked at JLCPCB
            s = s.replace('(property "Value" "ER_OLEDM0.91_1x-I2C"', '(property "Value" "HS91L02W2C01"')
            s = re.sub(r'\(property "Datasheet" "[^"]*"', '(property "Datasheet" "https://www.lcsc.com/datasheet/C5248081.pdf"', s, count=1)
            s = s.replace('(lib_id "Display_Graphic:ER_OLEDM0.91_1x-I2C")', '(lib_id "ayab-lib:OLED_128x32_I2C")')
            s = set_field(s, 'Reference', 203.2, 74.93, 0, 'left')
            s = set_field(s, 'Value', 203.2, 92.71, 0, 'left')
        if r == 'J14':
            # stock socket with staggered pads (friction-fit test header), kept in ayab-library
            s = s.replace('"Connector_PinSocket_2.54mm:PinSocket_1x08_P2.54mm_Vertical"', '"Library:PinSocket_1x08_P2.54mm_Vertical_Lock"')
        if r in ('RV1', 'RV2'):
            # local copy of the TC33X footprint with the silk clipped off the pads (JLCPCB 0.15 mm)
            s = s.replace('"Potentiometer_SMD:Potentiometer_Bourns_TC33X_Vertical"', '"Library:Potentiometer_Bourns_TC33X_Vertical"')
        if r == 'S1':
            s = set_field(s, 'Reference', 109.22, 160.02, 0, None)
            s = set_field(s, 'Value', 109.22, 162.56, 0, None)
        if r == 'U7':
            s = set_field(s, 'Reference', 359.41, 141.605, 0, 'left')
            s = set_field(s, 'Value', 359.41, 144.145, 0, 'left')
        if r in ('R15', 'R16', 'R17', 'R18'):
            x, y = map(float, re.search(r'\(at ([-\d.]+) ([-\d.]+)', s).groups())
            s = set_field(s, 'Reference', x - 0.635, y - 2.794, 90, 'left')
            s = set_field(s, 'Value', x + 0.635, y - 2.794, 90, 'right')
    if h == 'text' and s.startswith('(text "56k = 15V"'):
        s = s.replace('56k = 15V', 'R1 56k on CFG1: requests 15 V').replace('(size 0.762 0.762)', '(size 1.27 1.27)')
        s = s.replace('(at 134.62 124.46 0)', '(at 82.55 134.62 0)')
        s = s.replace('\t\t\t)\n\t\t)\n\t\t(uuid', '\t\t\t)\n\t\t\t(justify left)\n\t\t)\n\t\t(uuid', 1)
    if h == 'text' and s.startswith('(text "DP shorted'):
        s = s.replace('DP shorted to DM\\nto disable BC/QC\\nprotocols, only\\nPD is supported',
                      'DP shorted to DM: disables\\nBC/QC, only PD is supported')
        s = s.replace('(size 0.762 0.762)', '(size 1.27 1.27)').replace('(at 87.63 111.76 0)', '(at 82.55 129.54 0)')
        s = s.replace('\t\t\t)\n\t\t)\n\t\t(uuid', '\t\t\t)\n\t\t\t(justify left)\n\t\t)\n\t\t(uuid', 1)
    out.append(s)
out.append(t[last:])
body = re.sub(r'\n\t\x00', '', ''.join(out))
extra = (label('ALERT', 419.1, 134.62, 0) + label('ALERT', 419.1, 137.16, 180)
         + label('CMPREF', 392.43, 137.16, 0) + label('CFG1', 120.65, 107.95, 0))
# U5: display-looking symbol from ayab-lib instead of Display_Graphic:ER_OLEDM0.91_1x-I2C
i = body.index('\t\t(symbol "Display_Graphic:ER_OLEDM0.91_1x-I2C"'); d = 0; j = i
while True:
    d += {'(': 1, ')': -1}.get(body[j], 0)
    if d == 0 and body[j] == ')': break
    j += 1
body = body[:i] + open(__file__.rsplit('/', 1)[0] + '/oled_embedded.txt').read() + body[j + 1:]
# S1: thumb-wheel shaped symbol
sys.path.insert(0, __file__.rsplit('/', 1)[0]); import bldt
i, j = bldt.block(body, '\t\t(symbol "ayab-lib:BL-DT"'); body = body[:i] + bldt.redraw(body[i:j]) + body[j:]
# ERC: PWR_FLAGs on the undriven supply nets, no-connect marks on the unused ESP32 pins
lib = open(__file__.rsplit('/', 1)[0] + '/pwrflag_lib.txt').read()
i = body.index('\t\t(symbol "power:+15V"'); body = body[:i] + lib.lstrip('\t').join(['\t\t', '\n']) + body[i:]
tpl = re.search(r'\t\(symbol\n\t\t\(lib_id "power:\+5V"\).*?\n\t\)\n', body, re.S).group(0)
def flag(n, x, y):
    f = tpl.replace('"power:+5V"', '"power:PWR_FLAG"')
    f = re.sub(r'"#PWR\d+"', '"#FLG%02d"' % n, f)
    f = f.replace('(property "Value" "+5V"', '(property "Value" "PWR_FLAG"')
    f = re.sub(r'\(property "Description" [^\n]*', '(property "Description" "Special symbol for telling ERC where power comes from"', f)
    f = re.sub(r'\(uuid "[^"]+"\)', lambda m: '(uuid "%s")' % U(), f)
    f = re.sub(r'\n\t\t\(fields_autoplaced yes\)', '', f)
    f = re.sub(r'\(at [-\d.]+ [-\d.]+ \d+\)', '(at %g %g 0)' % (x, y), f)
    f = set_field(f, 'Reference', x, y - 1.905, 0, None)
    f = set_field(f, 'Value', x, y - 3.81, 0, None)
    return f
for n, (x, y) in enumerate([(90.17, 91.44), (49.53, 132.08), (295.91, 200.66), (152.4, 81.28)], 1):
    extra += flag(n, x, y)
extra += ('\t(wire\n\t\t(pts\n\t\t\t(xy 39.37 132.08) (xy 49.53 132.08)\n\t\t)\n\t\t(stroke\n\t\t\t(width 0)\n'
          '\t\t\t(type default)\n\t\t)\n\t\t(uuid "%s")\n\t)\n') % U()
for x, ys in ((137.16, (158.75, 161.29, 163.83, 166.37, 168.91, 181.61, 189.23)),
              (167.64, (161.29, 163.83, 166.37, 168.91, 176.53, 179.07, 181.61, 184.15, 186.69, 189.23, 191.77))):
    for y in ys:
        extra += '\t(no_connect\n\t\t(at %g %g)\n\t\t(uuid "%s")\n\t)\n' % (x, y, U())
i = body.index('\t(sheet_instances'); body = body[:i] + extra + body[i:]
open(sys.argv[2], 'w').write(body)

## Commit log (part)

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2025-02-22 Solenoid LED strip
2025-02-22 Move LEDs to be properly on top of solenoids
2025-05-09 Add design file PDFs to repo [skip ci]
2025-05-15 Move polarity symbol to ayab-library

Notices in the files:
ayab-shield/arduino_shield.kicad_pcb:
CC-BY-SA
